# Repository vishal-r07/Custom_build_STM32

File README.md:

# Customized STM32 Development Board

**Designer:** Vishal Meyyappan R
**Design Tool:** KiCad 9.0
**MCU:** STM32F103C8T6 (LQFP-48)

A compact, breakout-style STM32F103 development board built around a "Blue Pill"-class microcontroller, with dual power input (USB or barrel jack), onboard microSD storage for data logging, and broken-out USART/I2C/SWD headers for peripherals and debugging.

---

## 1. Overview

This board is designed as a general-purpose sensor data acquisition and logging platform. The core idea: read sensor values over I2C or USART, and persist them to a microSD card in real time, so the board can operate as a standalone data logger without needing a permanent connection to a PC. It can be powered either from USB (during development/debugging) or from an external DC supply via the barrel jack (for field/standalone deployment), with both sources safely combined so either one can be present without conflict.

### Key features

- STM32F103C8T6 microcontroller — 72 MHz Cortex-M3, 64KB Flash, 20KB RAM
- Dual power input: USB Micro-B **or** 7–12V DC barrel jack, diode-ORed together
- Onboard AMS1117-3.3 LDO regulator (3.3V logic/power rail)
- microSD card slot (SPI mode) for onboard data storage/logging
- USART1 header for serial communication (e.g. GPS, external logger, PC terminal)
- I2C2 header for sensor peripherals (IMUs, environmental sensors, RTCs, displays, etc.)
- SWD header for programming and debugging (ST-Link compatible)
- Reset button and status LED
- USB D+/D- routed directly to the MCU for native USB device applications (e.g. CDC virtual COM port, DFU bootloader use)
- 4x M2 mounting holes for mechanical enclosure mounting

---

## 2. Functional Blocks

### 2.1 Power Supply

The board accepts power from **either** of two sources, which are combined onto a single protected rail before regulation:

| Source | Connector | Voltage | Notes |
|---|---|---|---|
| USB | J1 (USB Micro-B) | 5V (VBUS) | Also carries D+/D- to the MCU for USB device functionality |
| DC Barrel Jack | J5 | 7–12V (typical wall adapter) | Center pin positive |

Both inputs pass through a dedicated Schottky diode (D2 for the barrel jack, D3 for USB VBUS) before joining onto a common rail. This "power-ORing" arrangement means:
- Either source can be connected and power the board independently.
- If both are connected simultaneously, the board draws from whichever is at the higher potential, without one source backfeeding into the other's connector — protecting a USB host (like a laptop) from being driven by the barrel jack supply, and vice versa.
- Reverse-polarity protection is inherent: if the barrel jack is wired backwards, the diode simply blocks conduction rather than damaging the board.

The combined rail feeds **U2 (AMS1117-3.3)**, a linear regulator that steps the input down to a clean 3.3V rail (`+3.3V`), which powers the MCU core, I/O, and the microSD card. `FB1` (a 120Ω ferrite bead) filters high-frequency noise on the USB VBUS path specifically, and `D1` (LED) with `R3` provides a visual power-on indicator.

A separate `+3.3VA` net is also present for the MCU's analog supply (`VDDA`), isolated with `C7`/`C8` to reduce noise coupling into the ADC/analog peripherals from the digital 3.3V rail.

### 2.2 Microcontroller (U1 — STM32F103C8T6)

The MCU is clocked from an 8 MHz external crystal (`Y1`, `Crystal_GND24`) with `C10`/`C11` (10pF) load capacitors, feeding the HSE (High-Speed External) oscillator input. `SW1` provides a manual reset (NRST), debounced by `C9` and pulled up by `R1`.

Boot mode selection (`BOOT0`) is available on the board for entering the built-in USB/UART bootloader if needed, alongside the SWD interface for hardware debugging.

### 2.3 USB Interface (J1)

A USB Micro-B connector routes `D+`/`D-` directly to the MCU's native USB peripheral pins (`PA11`/`PA12`), enabling USB device applications such as a virtual COM port (CDC), custom HID device, or DFU firmware updates. `R2` (1.5kΩ) pulls `USB_D-` up to 3.3V, a common requirement for the MCU to be recognized as a full-speed USB device without needing to bit-bang the pull-up in firmware.

### 2.4 DC Barrel Jack Input (J5)

For standalone/field operation where USB isn't available (e.g. powered by a wall adapter or battery pack), `J5` accepts a standard center-positive barrel connector. `C14`/`C15` provide bulk and high-frequency decoupling right at the input before the reverse-polarity diode `D2`.

### 2.5 microSD Card Storage (J6)

This is the board's primary logging mechanism. The microSD slot is wired in **SPI mode** (rather than native 4-bit SD mode, which this MCU's hardware doesn't support), using the MCU's SPI1 peripheral:

| J6 Pin | Native SD Function | SPI Mode Function | STM32 Pin |
|---|---|---|---|
| 2 (DAT3/CD) | Data line 3 / Card Detect | Chip Select (CS) | PA4 |
| 3 (CMD) | Command line | MOSI (DI) | PA7 |
| 5 (CLK) | Clock | SCK | PA5 |
| 7 (DAT0) | Data line 0 | MISO (DO) | PA6 |
| 1 (DAT2), 8 (DAT1) | Data lines 1–2 | Unused in SPI mode | Pulled up to 3.3V (R6–R8) |
| 4 (VDD) | Power | Power | +3.3V |
| 6 (VSS) | Ground | Ground | GND |
| 9 (SHIELD) | — | Mechanical shield | GND |

`C16` (100nF) decouples the card's local supply. A pull-up on `CS` (`PA4`) ensures the card remains deselected during MCU power-up/reset, before firmware has configured the pin as an active output — preventing bus contention during boot.

**Intended use case:** the board reads sensor data (e.g. from a device on the I2C2 header) at a fixed interval, formats it (e.g. as a CSV row with a timestamp), and writes it to a file on the SD card using a FAT filesystem library (FatFs) running over this SPI interface. This lets the board function as a self-contained data logger — sensor readings accumulate on the card over time and can be retrieved simply by removing the card and reading it on a PC, without needing a live connection to the board.

### 2.6 Communication Headers

| Header | Signals | Typical Use |
|---|---|---|
| J2 | SWDIO, SWCLK, 3.3V, GND | Programming/debugging via ST-Link or compatible SWD probe |
| J3 | USART1_TX, USART1_RX, 3.3V, GND | Serial communication — external modules (GPS, Bluetooth/BLE, PC terminal), or a second logging path |
| J4 | I2C2_SCL, I2C2_SDA, 3.3V, GND | Sensor peripherals — IMUs, environmental sensors (temperature/humidity/pressure), RTCs, OLED displays, etc. |

`R4`/`R5` (1.5kΩ) provide I2C bus pull-ups on the SDA/SCL lines.

### 2.7 Status & Control

- `D1` (LED) — power-on indicator, active whenever the 3.3V rail is present
- `SW1` — manual reset button (NRST)

### 2.8 Mechanical

Four M2 mounting holes (`H1`–`H4`) are provided at the board corners for enclosure mounting.

---

## 3. Typical Application: Sensor Data Logger

A representative use case this board is designed around:

1. Connect a sensor (e.g. an I2C temperature/humidity sensor, or an IMU) to the **J4 (I2C2)** header.
2. Firmware on the STM32 periodically polls the sensor over I2C.
3. Each reading is timestamped and formatted as a line of text (e.g. CSV: `timestamp,value1,value2`).
4. The line is written to a log file on the microSD card via **SPI1 + FatFs**.
5. The card can be removed and read on any PC, or the board can optionally stream the same data live over **J3 (USART1)** for real-time monitoring during development.

This makes the board suitable for applications like environmental monitoring stations, unattended data collection, portable measurement tools, or any project needing local, non-volatile storage of time-series sensor data without relying on cloud connectivity.

---

## 4. Power Architecture Summary

```
USB Micro-B (5V)  ──▶ D3 ──┐
                            ├──▶ Shared VIN net ──▶ AMS1117-3.3 (U2) ──▶ +3.3V rail ──▶ MCU, SD card, peripherals
Barrel Jack (7-12V) ─▶ D2 ──┘
```

Both sources are diode-ORed so either can power the board independently; the AMS1117-3.3 regulates whichever is present down to a clean 3.3V for the rest of the system.

---

## 5. Bill of Materials

| Reference | Qty | Value | Footprint | Datasheet |
|---|---|---|---|---|
| C1, C2, C3, C4, C9, C15, C16 | 7 | 100n | Capacitor_SMD:C_0402_1005Metric | ~ |
| C5, C14 | 2 | 10u | Capacitor_SMD:C_0603_1608Metric | ~ |
| C6 | 1 | 10n | Capacitor_SMD:C_0402_1005Metric | ~ |
| C7, C8 | 2 | 1u | Capacitor_SMD:C_0402_1005Metric | ~ |
| C10, C11 | 2 | 10p | Capacitor_SMD:C_0402_1005Metric | ~ |
| C12, C13 | 2 | 22u | Capacitor_SMD:C_0805_2012Metric | ~ |
| D1 | 1 | LED | LED_SMD:LED_0603_1608Metric | ~ |
| D2, D3 | 2 | D_Schottky | Diode_SMD:D_SMA | ~ |
| FB1 | 1 | 120R | Inductor_SMD:L_0603_1608Metric | ~ |
| H1, H2, H3, H4 | 4 | MountingHole | MountingHole:MountingHole_2.2mm_M2 | ~ |
| J1 | 1 | USB_B_Micro | Connector_USB:USB_Micro-B_Wuerth_629105150521 | ~ |
| J2, J3, J4 | 3 | Conn_01x04_Pin | Connector_PinSocket_2.54mm:PinSocket_1x04_P2.54mm_Vertical | ~ |
| J5 | 1 | Barrel_Jack | Connector_BarrelJack:BarrelJack_Horizontal | ~ |
| J6 | 1 | Micro_SD_Card | Connector_Card:microSD_HC_Wuerth_693072010801 | [Datasheet](https://www.we-online.com/components/products/datasheet/693072010801.pdf) |
| R1 | 1 | 10K | Resistor_SMD:R_0402_1005Metric | ~ |
| R2, R3, R4, R5 | 4 | 1k5 | Resistor_SMD:R_0402_1005Metric | ~ |
| R6, R7, R8 | 3 | 10k | Resistor_SMD:R_0402_1005Metric | ~ |
| SW1 | 1 | SW_SPDT | Button_Switch_SMD:SW_SPDT_PCM12 | ~ |
| U1 | 1 | STM32F103C8Tx | Package_QFP:LQFP-48_7x7mm_P0.5mm | [Datasheet](https://www.st.com/resource/en/datasheet/stm32f103c8.pdf) |
| U2 | 1 | AMS1117-3.3 | Package_TO_SOT_SMD:SOT-223-3_TabPin2 | [Datasheet](http://www.advanced-monolithic.com/pdf/ds1117.pdf) |
| Y1 | 1 | Crystal_GND24 | Crystal:Crystal_SMD_3225-4Pin_3.2x2.5mm | ~ |

**Total unique references:** 24 | **Total placed components:** ~50 (excluding mounting holes)

---

## 6. Firmware Notes

- **Toolchain:** STM32CubeIDE (or STM32CubeMX + preferred IDE/toolchain)
- **SD card access:** SPI1 peripheral + FatFs middleware (SD-over-SPI driver); recommend low clock speed (~400 kHz) during card initialization, then increasing to a few MHz for normal read/write operations
- **I2C sensor communication:** I2C2 peripheral (`PB10`/`PB11`), 3.3V logic
- **Serial/debug output:** USART1 (`PA9`/`PA10`), standard TTL-level UART, 3.3V logic
- **Debugging:** Standard SWD (`PA13`/`PA14`) — compatible with ST-Link V2/V3 or any SWD-capable probe
- **USB:** Native USB device peripheral (`PA11`/`PA12`) — usable for CDC virtual COM port, custom HID, or DFU bootloader entry

---

**PCB Editor**

**3D VIEW**

I have attached Schematic sheet as output.pdf

---

## Designed by Vishal Meyyappan R

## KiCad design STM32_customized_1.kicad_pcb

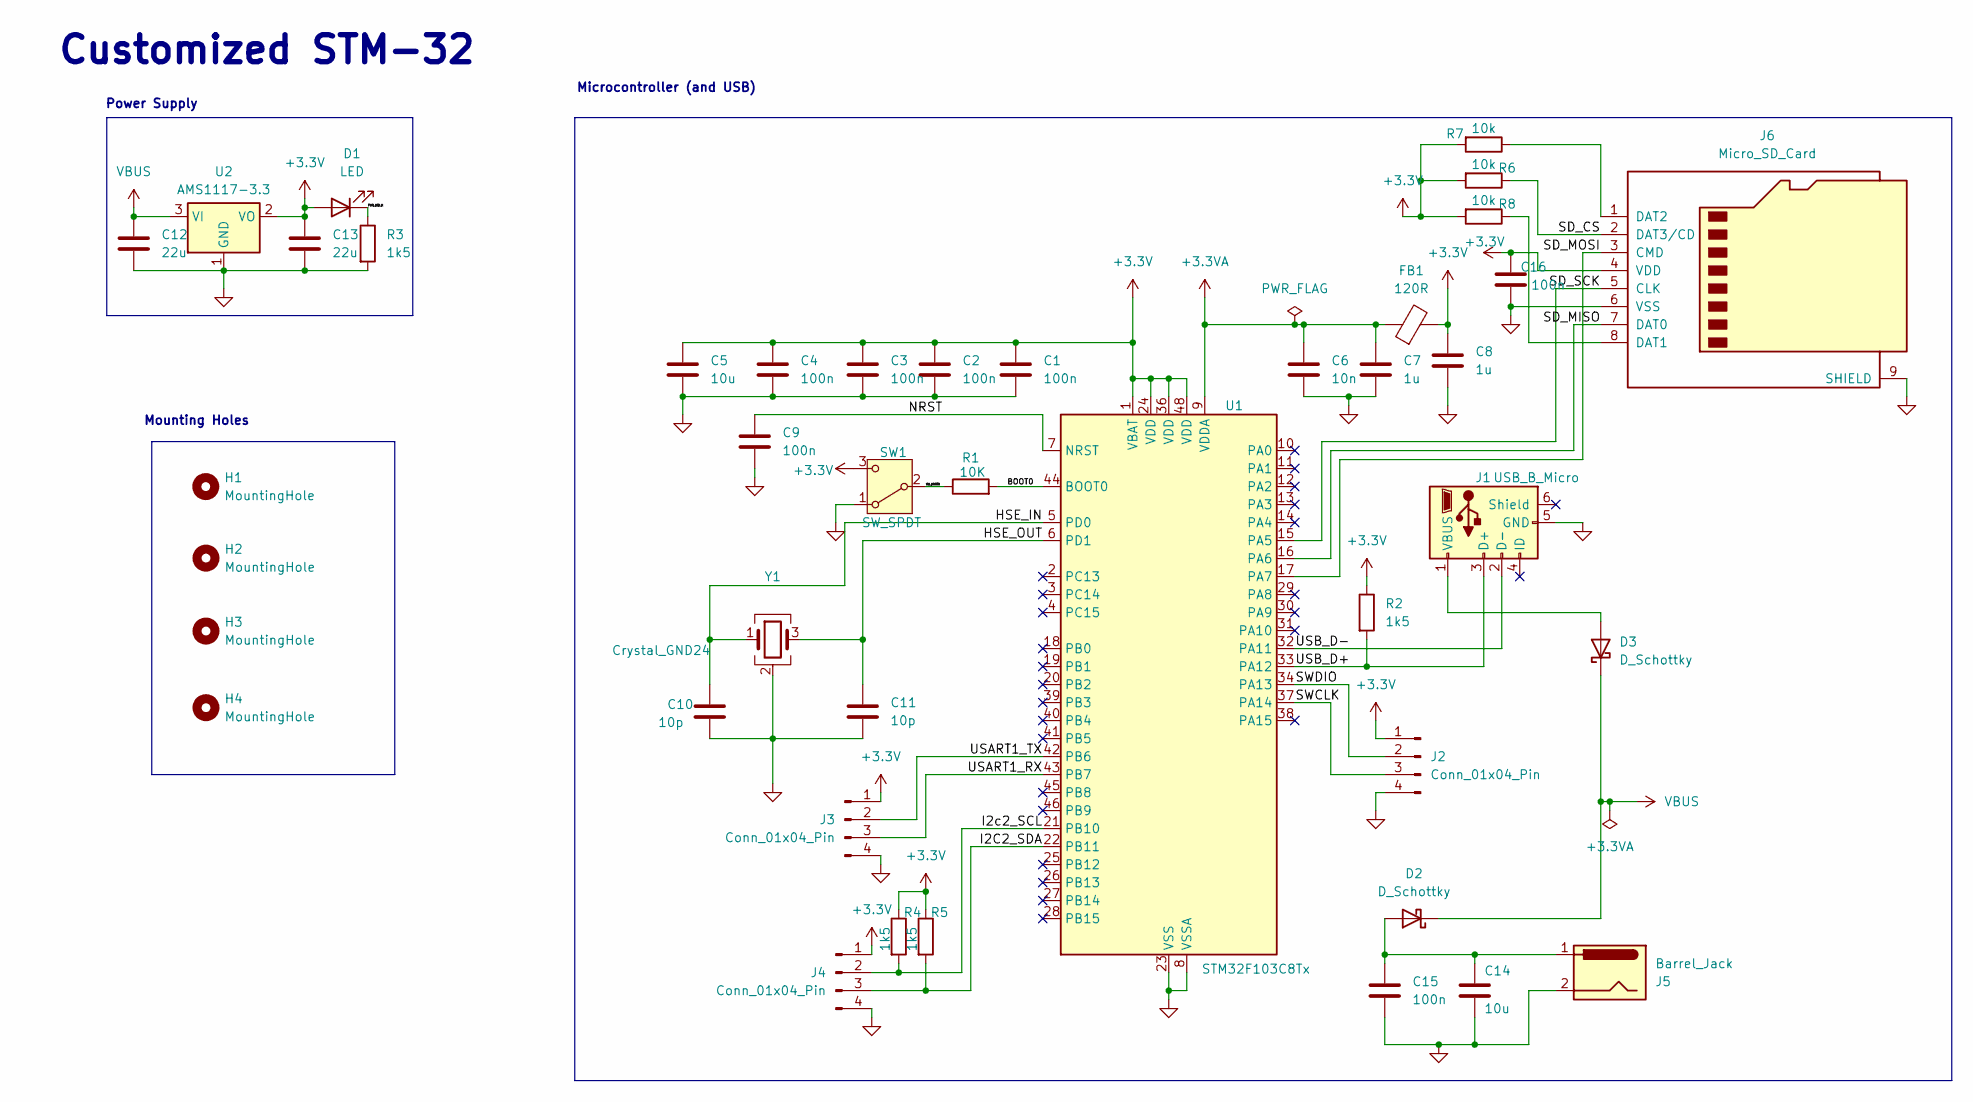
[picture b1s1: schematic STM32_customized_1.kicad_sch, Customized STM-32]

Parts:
C1, C2, C3, C4, C9, C15, C16: 100n; C_0402_1005Metric
C5, C14: 10u; C_0603_1608Metric
C6: 10n; C_0402_1005Metric
C7, C8: 1u; C_0402_1005Metric
C10, C11: 10p; C_0402_1005Metric
C12, C13: 22u; C_0805_2012Metric
D1: LED; LED_0603_1608Metric
D2, D3: D_Schottky; D_SMA
FB1: 120R; L_0603_1608Metric
H1, H2, H3, H4: MountingHole; MountingHole_2.2mm_M2
J1: USB_B_Micro; USB_Micro-B_Wuerth_629105150521
J2, J3, J4: Conn_01x04_Pin; PinSocket_1x04_P2.54mm_Vertical
J5: Barrel_Jack; BarrelJack_Horizontal
J6: Micro_SD_Card; microSD_HC_Wuerth_693072010801
R1: 10K; R_0402_1005Metric
R2, R3, R4, R5: 1k5; R_0402_1005Metric
R6, R7, R8: 10k; R_0402_1005Metric
SW1: SW_SPDT; SW_SPDT_PCM12
U1: STM32F103C8Tx; LQFP-48_7x7mm_P0.5mm
U2: AMS1117-3.3; SOT-223-3_TabPin2
Y1: Crystal_GND24; Crystal_SMD_3225-4Pin_3.2x2.5mm

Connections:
+3.3V: C1.1, C2.1, C3.1, C4.1, C5.1, C8.1, C13.1, C16.1, D1.2 (A), FB1.2, J2.1, J3.1, J4.1, J6.4 (VDD), R2.1, R4.1, R5.1, R6.2, R7.2, R8.2, SW1.3 (C), U1.1 (VBAT), U1.24 (VDD), U1.36 (VDD), U1.48 (VDD), U2.2 (VO)
+3.3VA: C6.1, C7.1, FB1.1, U1.9 (VDDA)
/BOOT0: R1.2, U1.44 (BOOT0)
/HSE_IN: C10.1, U1.5 (PD0), Y1.1
/HSE_OUT: C11.1, U1.6 (PD1), Y1.3
/I2C2_SDA: J4.3, R5.2, U1.22 (PB11)
/I2c2_SCL: J4.2, R4.2, U1.21 (PB10)
/NRST: C9.1, U1.7 (NRST)
/PWR_LED_K: D1.1 (K), R3.1
/SD_CS: J6.2 (DAT3/CD), R6.1
/SD_MISO: J6.7 (DAT0), U1.16 (PA6)
/SD_MOSI: J6.3 (CMD), U1.17 (PA7)
/SD_SCK: J6.5 (CLK), U1.15 (PA5)
/SWCLK: J2.3, U1.37 (PA14)
/SWDIO: J2.2, U1.34 (PA13)
/SW_BOOT0: R1.1, SW1.2 (B)
/USART1_RX: J3.3, U1.43 (PB7)
/USART1_TX: J3.2, U1.42 (PB6)
/USB_D+: J1.3 (D+), R2.2, U1.33 (PA12)
/USB_D-: J1.2 (D-), U1.32 (PA11)
GND: C1.2, C2.2, C3.2, C4.2, C5.2, C6.2, C7.2, C8.2, C9.2, C10.2, C11.2, C12.2, C13.2, C14.2, C15.2, C16.2, J1.5 (GND), J2.4, J3.4, J4.4, J5.2, J6.6 (VSS), J6.9 (SHIELD), R3.2, SW1.1 (A), U1.8 (VSSA), U1.23 (VSS), U1.35 (VSS), U1.47 (VSS), U2.1 (GND), Y1.2 (G), Y1.4 (G)
unnamed: C14.1, C15.1, D2.2 (A), J5.1
unnamed: D3.2 (A), J1.1 (VBUS)
unnamed: J6.8 (DAT1), R8.1
unnamed: J6.1 (DAT2), R7.1
VBUS: C12.1, D2.1 (K), D3.1 (K), U2.3 (VI)

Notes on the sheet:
Mounting Holes
Microcontroller (and USB)
Power Supply
Customized STM-32

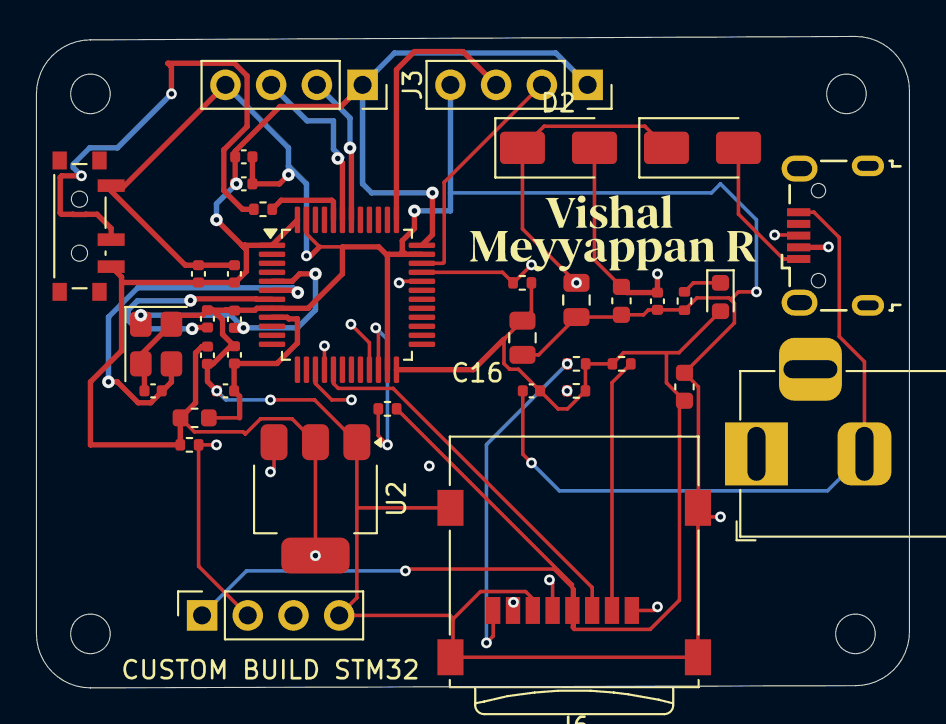
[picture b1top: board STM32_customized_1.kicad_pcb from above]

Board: 4 copper layers, 48.5 x 36.2 mm, 42 parts (0 on the bottom side), 26 nets.

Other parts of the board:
CUSTOM BUILD STM32: MountingHole; MountingHole_2.2mm_M2
